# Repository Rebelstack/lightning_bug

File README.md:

# lightning_bug
EAGLE hardware design and production files for Lightning Bug
# Product Description

<br />
Lightning Bug is an acceleration-activated PWM current supply.  Inspired by flying trapeze, 
it is designed to be worn on the body and and connected to a strip of LEDs.  The LEDs are lit
with an intensity that varies with acceleration.  Powered with a standard 9V battery,
Lightning Bug provides a maximum of close to 1A which is divided among the number of
parallel connected LEDs.
# Release Notes
-It is somewhat difficult to insert and remove battery with the battery clip specified.

-R1 and C7 form a low pass recommended by the accelerometer, but may not be necessary 
for this application.  Replace R1 with a 0 Ohm short and do not populate C7 to remove.

-Standard 4-40 screws/nuts can be used to affix the battery clip to the PCB, but two
of the four mounting holes have components close which may interfere.
# Licensing
This work is licensed under a Creative Commons Attribution-ShareAlike 4.0 International License

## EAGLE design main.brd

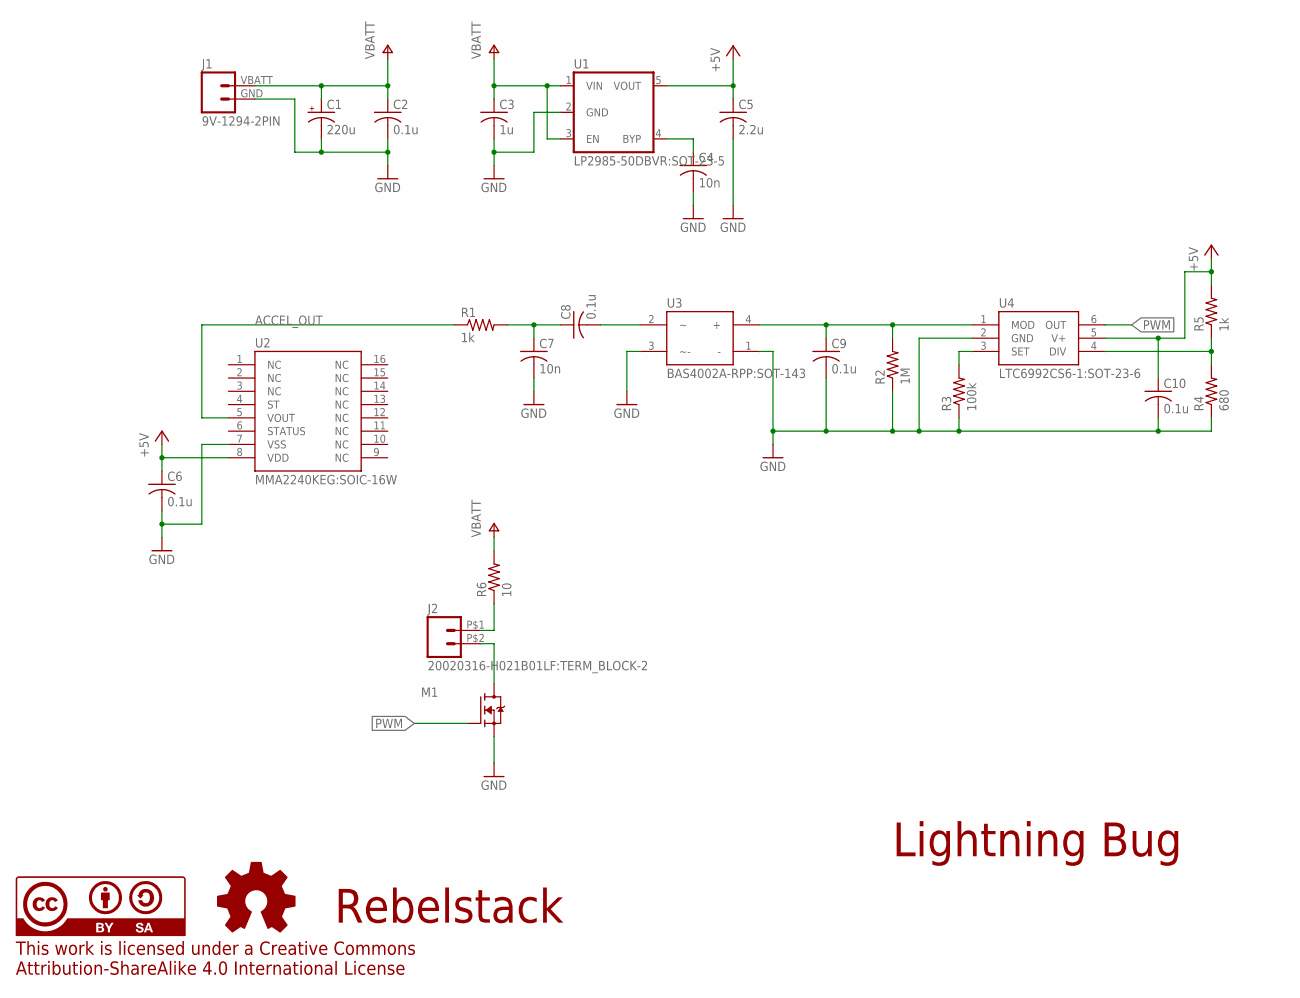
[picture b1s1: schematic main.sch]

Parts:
C1: 220u; D/7343-31W
C2, C6, C8, C9, C10: 0.1u; C0805
C3: 1u; C0805
C4, C7: 10n; C0805
C5: 2.2u; C0805
J1: 9V-1294-2PIN; 9V-THRU
J2: 20020316-H021B01LF:TERM_BLOCK-2; TERM_BLOCK-2
M1: IRLML2502TRPBF:SOT-23-3; SOT-23-3
R1, R5: 1k; M0805
R2: 1M; M0805
R3: 100k; M0805
R4: 680; M0805
R6: 10; R2512
U1: LP2985-50DBVR:SOT-23-5; SOT-23-5
U2: MMA2240KEG:SOIC-16W; SOIC-16W
U3: BAS4002A-RPP:SOT-143; SOT-143
U4: LTC6992CS6-1:SOT-23-6; SOT-23-6
U$4: CC-BY-SA-4.0-INT-PCB; CC-BY-SA-4.0-INT
U$5: OSHW-LOGO-PCB; OSHW-LOGO

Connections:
+5V: C5.1, C6.1, C10.1, R5.2, U1.5 (VOUT), U2.8 (VDD), U4.5 (V+)
ACCEL_OUT: R1.1, U2.5 (VOUT)
GND: C1.-, C2.2, C3.2, C4.2, C5.2, C6.2, C7.2, C9.2, C10.2, J1.GND (2), M1.2 (S), R2.1, R3.1, R4.1, U1.2 (GND), U2.7 (VSS), U3.1 (-), U3.3 (~-), U4.2 (GND)
unnamed: C4.1, U1.4 (BYP)
unnamed: C8.2, U3.2
unnamed: C9.1, R2.2, U3.4 (+), U4.1 (MOD)
unnamed: R4.2, R5.1, U4.4 (DIV)
unnamed: C7.1, C8.1, R1.2
unnamed: J2.P$1 (1), R6.1
unnamed: R3.2, U4.3 (SET)
unnamed: J2.P$2 (2), M1.3 (D)
PWM: M1.1 (G), U4.6 (OUT)
VBATT: C1.+, C2.1, C3.1, J1.VBATT (1), R6.2, U1.1 (VIN), U1.3 (EN)

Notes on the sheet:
Rebelstack
Lightning Bug

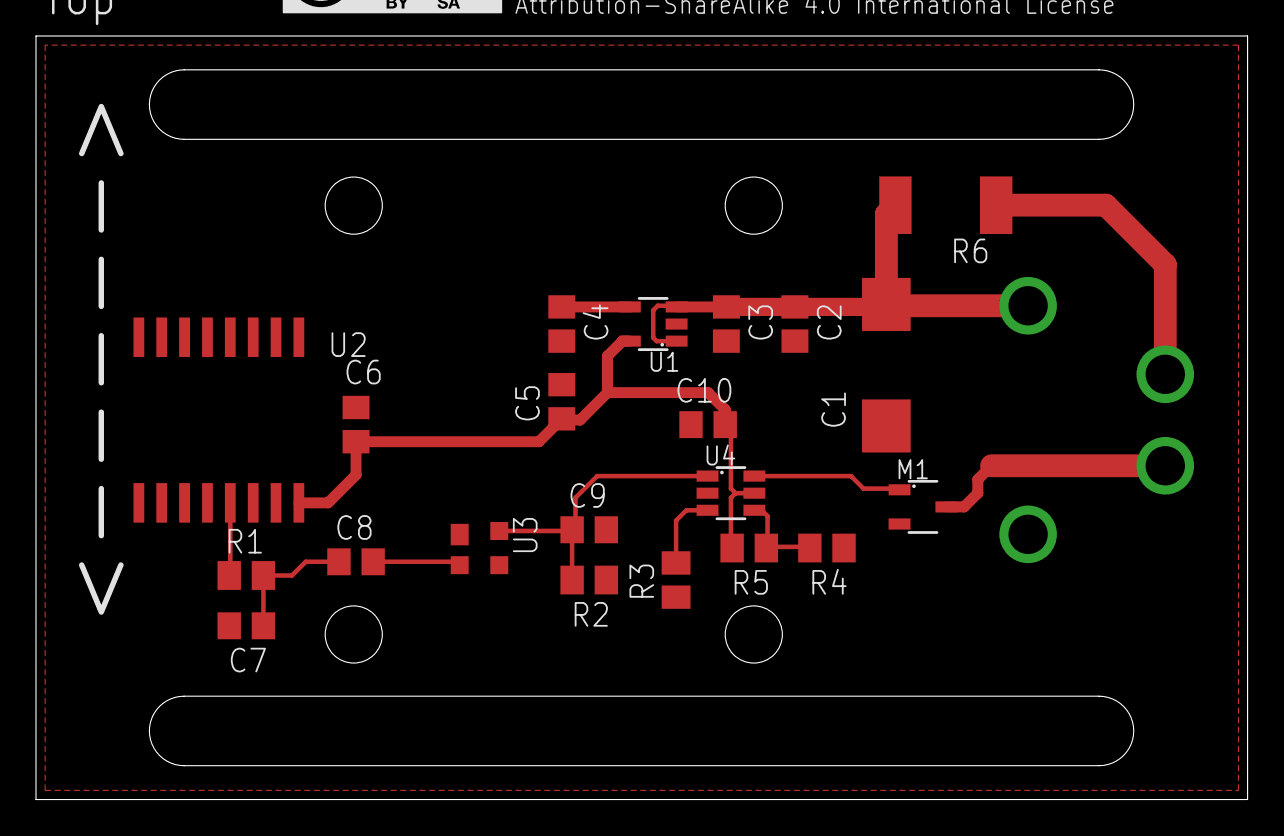
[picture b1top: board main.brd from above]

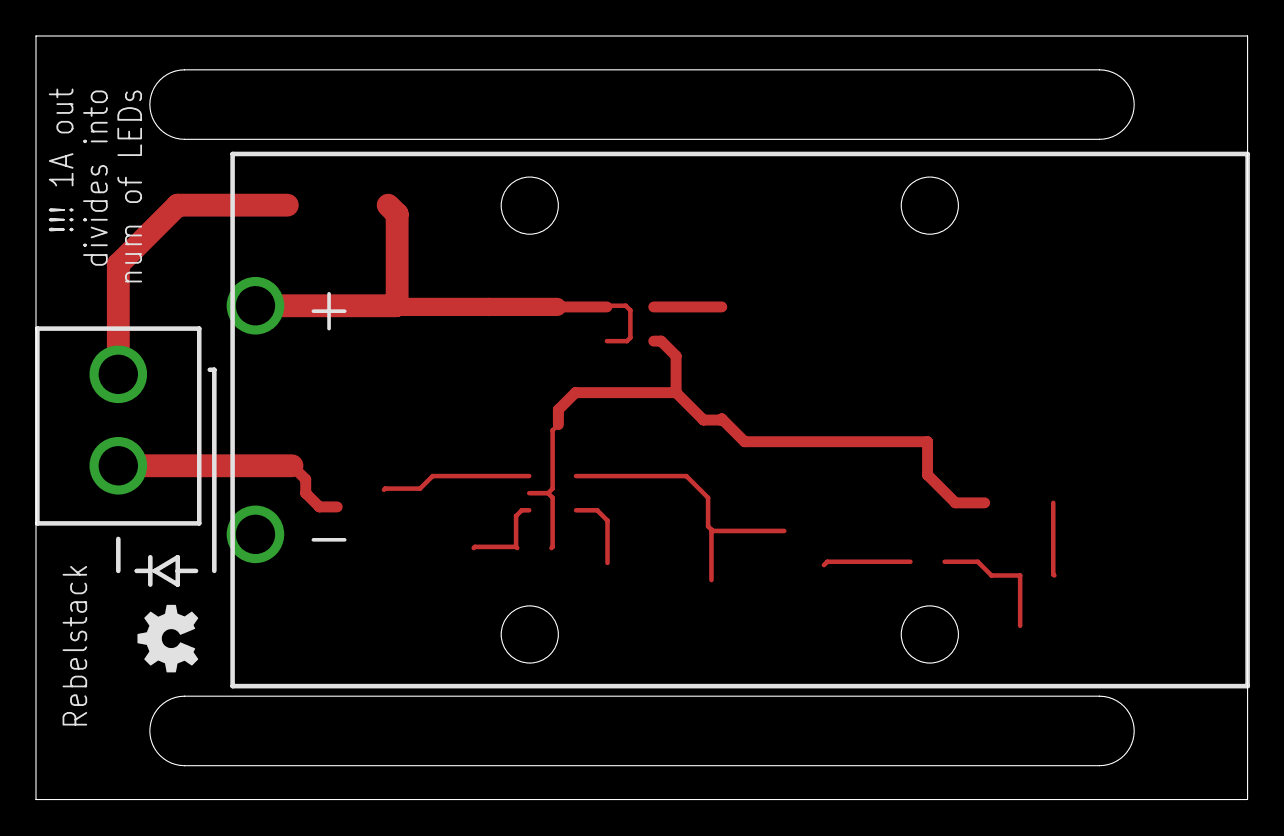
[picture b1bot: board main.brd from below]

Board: 2 copper layers, 67.3 x 42.4 mm, 25 parts (3 on the bottom side), 13 nets.

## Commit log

2016-06-13 added submodule for eagle library files
2016-06-13 added distributor and distributor p/n attributes to parts
2016-06-13 pulled latest commit of submodule
2016-06-13 Update README.md
    added license info
2016-06-15 -removing .epf eagle project file from source control -adding image for product description
2016-06-15 -reduced lightning bug image size
2016-06-21 adding BOM to project
2017-02-23 adding polyalphabetic cipher code
2017-02-25 Update cipher.txt
    -fixed typo
2017-02-28 -removed cipher

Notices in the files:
parts and their libraries:
rebelStack: Creative Commons BY-SA-4.0 International Notice Silkscreen
rebelStack: Creative Commons Attribution-Share Alike Notice Symbol
rebelStack: Creative Commons BY-SA-4.0 International License, Symbol and Silkscreen
